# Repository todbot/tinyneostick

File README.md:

# tinyneostick

https://github.com/user-attachments/assets/76d0b64d-8d65-415a-80bf-0ed369d2d5fe

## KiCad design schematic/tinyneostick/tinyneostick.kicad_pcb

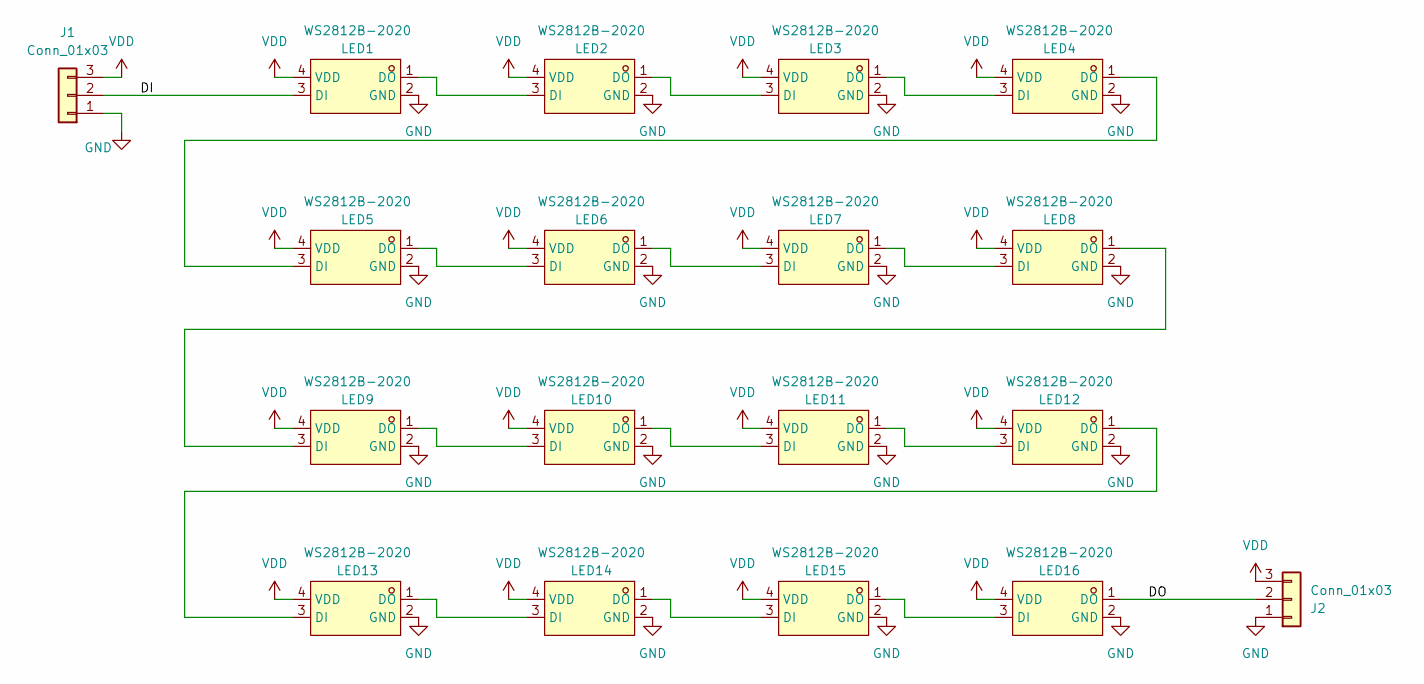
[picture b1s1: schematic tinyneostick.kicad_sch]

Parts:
J1, J2: Conn_01x03; Pins_1x03_P2.54mm_Horizontal_SMT_bigger; Part Number 1-0301FBV0T
LED1, LED2, LED3, LED4, LED5, LED6, LED7, LED8, LED9, LED10, LED11, LED12, LED13, LED14, LED15, LED16: WS2812B-2020; LED-SMD_4P-L2.0-W2.0-TL_WS2812B-2020; LCSC Part C965555

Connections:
/DI: J1.2, LED1.3 (DI)
/DO: J2.2, LED16.1 (DO)
GND: J1.1, J2.1, LED1.2 (GND), LED2.2 (GND), LED3.2 (GND), LED4.2 (GND), LED5.2 (GND), LED6.2 (GND), LED7.2 (GND), LED8.2 (GND), LED9.2 (GND), LED10.2 (GND), LED11.2 (GND), LED12.2 (GND), LED13.2 (GND), LED14.2 (GND), LED15.2 (GND), LED16.2 (GND)
unnamed: LED1.1 (DO), LED2.3 (DI)
unnamed: LED2.1 (DO), LED3.3 (DI)
unnamed: LED3.1 (DO), LED4.3 (DI)
unnamed: LED4.1 (DO), LED5.3 (DI)
unnamed: LED5.1 (DO), LED6.3 (DI)
unnamed: LED6.1 (DO), LED7.3 (DI)
unnamed: LED7.1 (DO), LED8.3 (DI)
unnamed: LED8.1 (DO), LED9.3 (DI)
unnamed: LED9.1 (DO), LED10.3 (DI)
unnamed: LED10.1 (DO), LED11.3 (DI)
unnamed: LED11.1 (DO), LED12.3 (DI)
unnamed: LED12.1 (DO), LED13.3 (DI)
unnamed: LED13.1 (DO), LED14.3 (DI)
unnamed: LED14.1 (DO), LED15.3 (DI)
unnamed: LED15.1 (DO), LED16.3 (DI)
VDD: J1.3, J2.3, LED1.4 (VDD), LED2.4 (VDD), LED3.4 (VDD), LED4.4 (VDD), LED5.4 (VDD), LED6.4 (VDD), LED7.4 (VDD), LED8.4 (VDD), LED9.4 (VDD), LED10.4 (VDD), LED11.4 (VDD), LED12.4 (VDD), LED13.4 (VDD), LED14.4 (VDD), LED15.4 (VDD), LED16.4 (VDD)

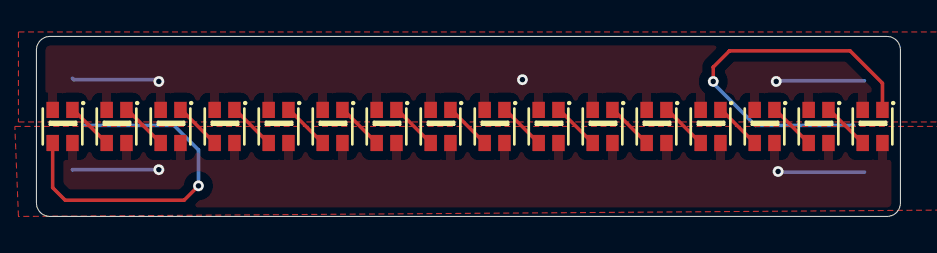
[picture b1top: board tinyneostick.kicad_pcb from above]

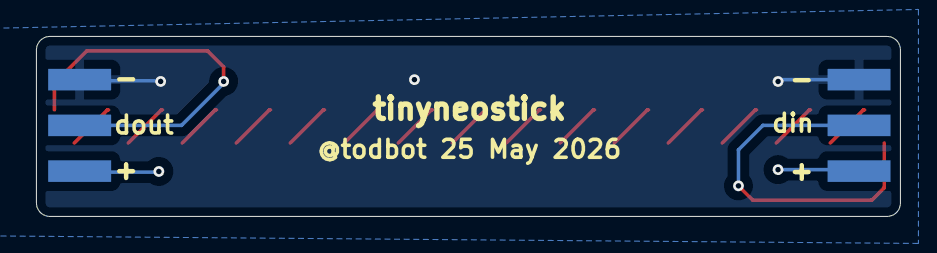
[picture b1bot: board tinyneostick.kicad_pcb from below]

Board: 2 copper layers, 48.0 x 10.0 mm, 18 parts (2 on the bottom side), 19 nets.

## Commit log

2026-03-25 first
2026-03-25 smd version, 48mm x 7.8mm, cannot be PCBAd by JLC tho
2026-03-26 48mm x 10mm version
2026-03-26 small fixes
